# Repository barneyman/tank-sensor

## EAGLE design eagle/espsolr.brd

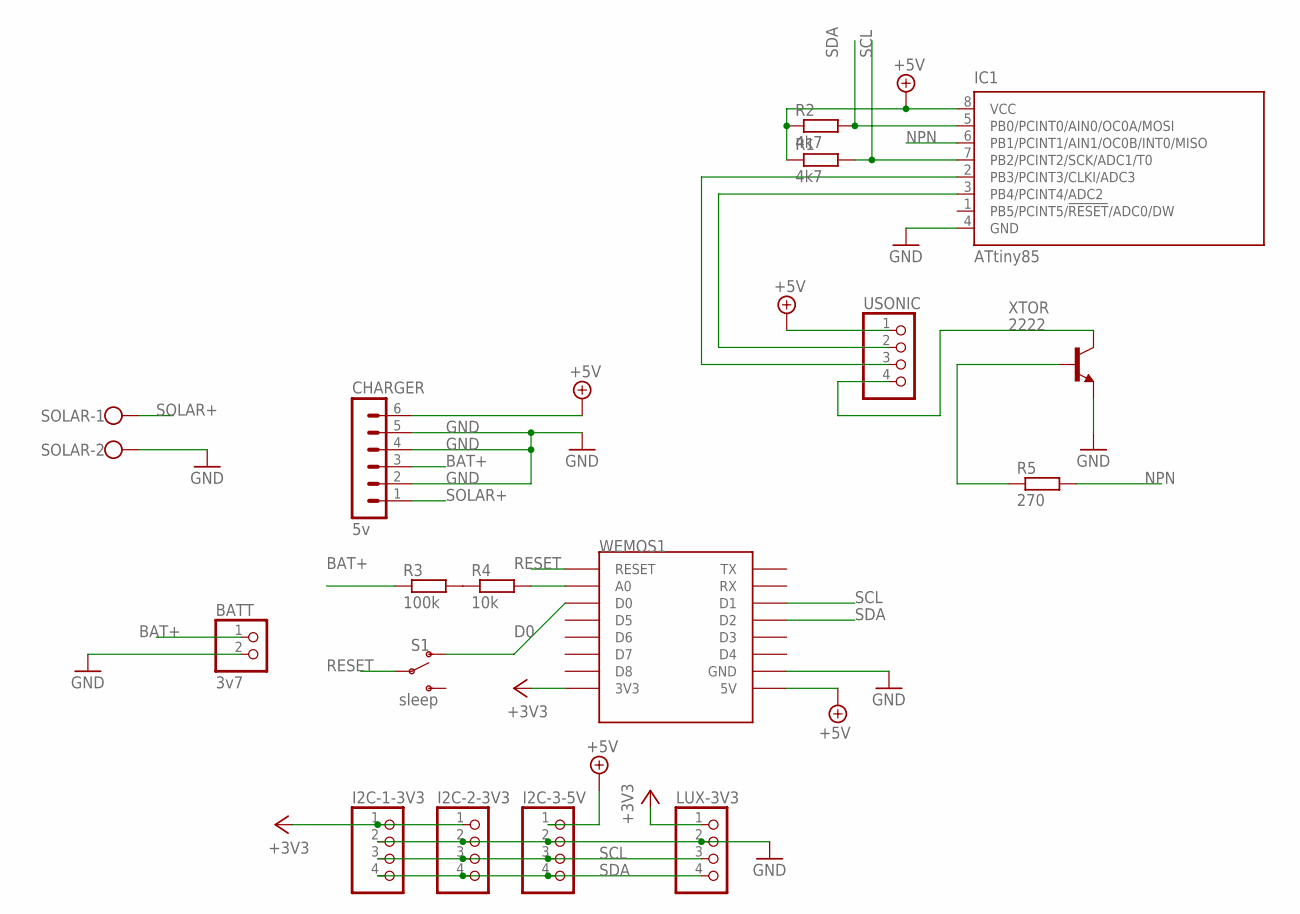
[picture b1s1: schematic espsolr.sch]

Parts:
BATT: 3v7; 1X02
CHARGER: 5v; MA06-1
I2C-1-3V3, I2C-2-3V3, I2C-3-5V: PINHD-1X4; 1X04
IC1: ATtiny85; DIL08
LUX-3V3: PINHD-1X4; 1X04
R1, R2: 4k7; 0204/7
R3: 100k; 0204/7
R4: 10k; 0204/7
R5: 270; 0204/7
S1: sleep; SWITCH_SPDT_PTH_11.6X4.0MM
SOLAR: W237-102
USONIC: PINHD-1X4; 1X04
WEMOS1: WEMOS-D1-MINI
XTOR: 2222; TO92-EBC

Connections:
+3V3: I2C-1-3V3.1, I2C-2-3V3.1, LUX-3V3.1, WEMOS1.3V3
+5V: CHARGER.6, I2C-3-5V.1, IC1.8 (VCC), R1.1, R2.1, USONIC.1, WEMOS1.5V
BAT+: BATT.1, CHARGER.3, R3.1
D0: S1.1 (O), WEMOS1.D0
GND: BATT.2, CHARGER.2, CHARGER.4, CHARGER.5, I2C-1-3V3.2, I2C-2-3V3.2, I2C-3-5V.2, IC1.4 (GND), LUX-3V3.2, SOLAR.2, WEMOS1.GND, XTOR.E
unnamed: R3.2, R4.1
unnamed: R4.2, WEMOS1.A0
unnamed: IC1.2 (PB3/PCINT3/CLKI/ADC3), USONIC.3
unnamed: IC1.3 (PB4/PCINT4/ADC2), USONIC.2
unnamed: USONIC.4, XTOR.C
unnamed: R5.1, XTOR.B
NPN: IC1.6 (PB1/PCINT1/AIN1/OC0B/INT0/MISO), R5.2
RESET: S1.2, WEMOS1.RESET
SCL: I2C-1-3V3.3, I2C-2-3V3.3, I2C-3-5V.3, IC1.7 (PB2/PCINT2/SCK/ADC1/T0), LUX-3V3.3, R1.2, WEMOS1.D1
SDA: I2C-1-3V3.4, I2C-2-3V3.4, I2C-3-5V.4, IC1.5 (PB0/PCINT0/AIN0/OC0A/MOSI), LUX-3V3.4, R2.2, WEMOS1.D2
SOLAR+: CHARGER.1, SOLAR.1

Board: 2 copper layers, 17 parts (0 on the bottom side), 16 nets, no tracks yet.

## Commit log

2018-02-06 LOTS of stack mem fixes
2018-02-06 Changed sample period, removed cruft, only append to SD if something goes wrong
2018-02-07 cleaned up the APIkey stuff - need to search for sheets by name
2018-02-07 when it boots cold it offers an AP to configure it on
2018-02-10 csan OTA now - added mnissing files
2018-02-12 added some AP mode timeouts to save battery when factory condition
2018-02-12 fixed cached upload, more debug
2018-02-12 fix some STUPID loop logic
2018-02-12 cache anything not sent, finesse the update handling and bugfixes
2018-02-12 try to align with the clock, so every 5 mintes will be 5/10/15 ... changed internal sample to minutes from seconds
2018-02-12 handle underflow
2018-02-12 cruft
2018-02-12 can't remember
2018-02-13 VS required files
2018-02-14 take 3 samples from the sonar
2018-02-24 added lux and lipo reading, moved i2c to other pins to get some gpios back, changed ultrasonic to PW mode
2018-03-01 added version to config, increased R in analog pin to cater for charging, added sampling
2018-03-05 added call to get last seen data, for the lux meter and robot lights
2018-03-05 lux and last details
2018-04-10 added board
2018-04-10 excluded eagle cruft
2018-05-27 removed the 12v i2c from the board - what was i thinking?
2018-06-25 updated board and created gerbers
2018-07-02 added debugger, changed to use the atUltra
2018-07-03 some instructions on how to install (setup.py may be better) default to running script dir
2018-07-03 added setup.py
2018-07-03 changed to reflect setup.py
2018-07-04 some cleanup
2018-07-07 fixed the analog pin to battery - duh!
2018-07-07 tweaked size and layers
2018-07-19 single thread worker, fixed adding failed rows, more debug
2018-07-19 ignore config dir
2018-07-19 changed debug level, leave led on during runtime, spelling mistakes
2018-07-19 ignore upgrades
2018-07-19 tweaks
2018-07-20 return join result, changed xmlhttprequest to fetch, added error css
2018-07-26 changed default dir to 'above me'
2018-09-12 debug
2018-09-12 add json to persisted last values
2018-10-15 added variable sleep time, fn( lipoV )
2019-01-21 updated code for depracated changes in core - crashes fairly quick - don't know why
2019-10-13 fixed crash i think

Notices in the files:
parts and their libraries:
SparkFun-Switches: Licensing: Creative Commons ShareAlike 4.0 International - https://creativecommons.org/licenses/by-sa/4.0
